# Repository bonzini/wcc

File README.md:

This is the repository for my first ESP8266 project.
The idea is to connect two gamepads wirelessly to the Raspberry Pi.
Of course I could just use a Wiimote and a Bluetooth dongle, but
I am trying to learn things!  So I plan to connect the ESP8266 to two
Wii Classic Controllers, which speak I2C; the ESP8266 then sends events
as UDP packets over wifi; on the Raspberry Pi side, a simple C
program (wcc-client) runs on the Raspberry Pi and exposes a virtual
gamepad via /dev/uinput.

To simplify the code on the microcontroller, the UDP protocol is
simply the I2C packets.  I first developed the client using an
"emulated" gamepad, wcc-server: this is a Linux program that
connects to /dev/input/eventNN and converts keypresses to I2C packets.
You can also use it to play with a USB keyboard instead of a gamepad.

The ESP8266 expects gamepad 1 on GPIOs 14/2 (SCL/SDA) and gamepad 2
on pins 4/0.  I have designed a simple PCB that plugs on top of a
Sparkfun thing like a "shield" and automatically wires two I2C buses
to the right pins.  You can find it in the `eagle` subdirectory (when
I have some time I will redo it in KiCAD).

The ESP8266 sketch contains a simple configuration portal.  After
uploading the sketch, it will create an access point named "ESP8266 xxyy"
where xxyy are two hexadecimal digits.  Connect to the access point and
point the browser to 192.168.4.1; enter your SSID name and password and
wait for the ESP8266 to reboot.  However the IP of the client is hard-coded
in the sketch for now.

Configuration data is persistent as it's stored in the ESP8266 EEPROM.  To
clear it, ground pin 5 before powering the ESP8266; the EEPROM will be
cleared and the configuration portal will appear.  Failure to connect
to the stored SSID will trigger the configuration portal too.

The next steps include:

* building a nice enclosure for the thing

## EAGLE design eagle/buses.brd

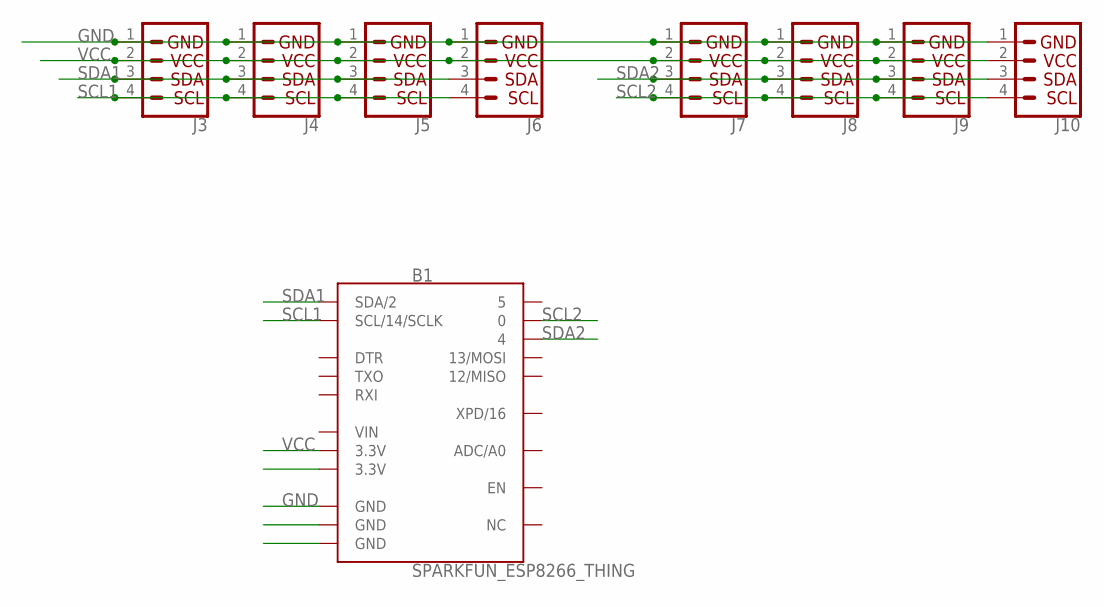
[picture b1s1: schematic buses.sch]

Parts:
B1: SPARKFUN_ESP8266_THING
J3, J4, J5, J6, J7, J8, J9, J10: I2C_STANDARD; 1X04

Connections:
GND: B1.GND@1 (GND), B1.GND@2 (GND), B1.GND@3 (GND), J3.1, J4.1, J5.1, J6.1, J7.1, J8.1, J9.1, J10.1
SCL1: B1.SCL (SCL/14/SCLK), J3.4, J4.4, J5.4, J6.4
SCL2: B1.0, J7.4, J8.4, J9.4, J10.4
SDA1: B1.SDA (SDA/2), J3.3, J4.3, J5.3, J6.3
SDA2: B1.4, J7.3, J8.3, J9.3, J10.3
VCC: B1.3.3V@1 (3.3V), B1.3.3V@2 (3.3V), J3.2, J4.2, J5.2, J6.2, J7.2, J8.2, J9.2, J10.2
VIN: B1.VIN

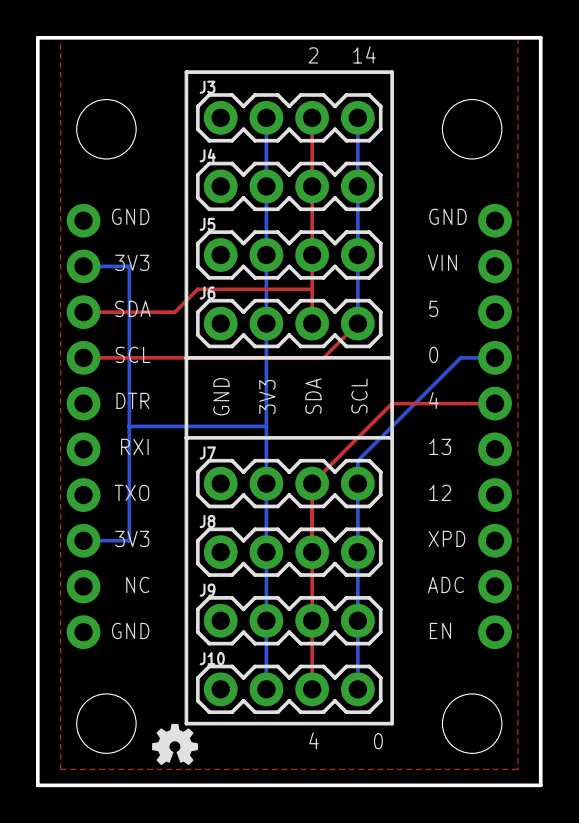
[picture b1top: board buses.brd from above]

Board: 2 copper layers, 27.9 x 41.5 mm, 10 parts (0 on the bottom side), 6 nets.

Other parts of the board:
U$1: OSHW-LOGO-MINI

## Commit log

2017-06-18 add client
2017-06-18 add server
2017-06-18 wcc-server: select is on the left, map it to 1
2017-06-18 add SYN_REPORT
2017-06-18 add Makefile
2017-06-18 invert button bits in I2C protocol
2017-06-18 reuse WCC_I2C_LENGTH
2017-06-18 add static
2017-06-20 add systemd units
2017-06-20 do not flood
2017-06-20 use SYN_REPORT in server too
2017-06-20 fix comments
2017-06-20 README
2017-06-21 add retroarch config
2017-06-21 handle POLLHUP
2017-09-30 done!!
2017-09-30 add license :)
2017-09-30 add board
    This is a simple board for the Sparkfun Thing to provide power and
    ground rails and two I2C buses. The board was designed with Eagle,
    but the directory includes the gerber files in buses.zip, so you do
    not need to run proprietary software to have the board manufactured.
    I will redo it with KiCAD when I have some time.
2017-10-04 invert L/R with L2/R2
    The bottom row is much easier to press.
2019-01-31 analog does not need calibration on my gamepad...
2019-01-31 add kodi 18 controller file
2019-01-31 support old setup API

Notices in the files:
parts and their libraries:
SparkFun-Boards: Licensing: Creative Commons ShareAlike 4.0 International - https://creativecommons.org/licenses/by-sa/4.0
